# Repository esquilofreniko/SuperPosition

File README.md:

**SuperPosition – Rev 1**

**Bill of Materials:**

|Function / Name 		|# |Note 								|Part Number 		|
|-----------------------|--|------------------------------------|-------------------|
|MCU Teensy 3.5/3.6 	|1 |Cut USB power trace 				|DEV-14057 			|
|Display OLED SSD1306 	|1 |SSD1306 / SPI / 0.96’’ / 128x64 [1] | 					|
|Adafruit NeoTrellis 	|1 |4x4 RGB LED Button Matrix [2] 		|Mouser: 485-1616 	|
|Silicone 4x4 Keypad 	|1 |Silicone Elastomer Button Keypad [3]|Mouser: 485-1611 	|
|Rotary Encoder 		|2 |24 Pulse Mechanical Rotary Encoder 	|PEC11R-4220F -S0024|
|Tactile Switch 		|2 |9.4mm Black Button Tactile Switch 	|2-1825910-7 		|
|3.5mm Jacks 			|12 |“Thonkiconn” Mono Jacks from Thonk |PJ398SM 			|
|DAC MCP4922 			|2 |12-bit Digital to Analog Converter 	|MCP4922-E/P 		|
|Op-amp MCP6004 		|1 |Operational Amplifier 				|MCP6004-E/P 		|
|Op-amp TL04CN 			|2 |Operational Amplifier 				|TL074CN 			|
|Regulator L7805 		|1 |5V Voltage Regulator 				|L7805CP 			|
|Diode 1N5817 			|2 |Through Hole 						|1N5817 			|
|Resistor 100k SMD 0805 |24|0.1% 								| 					|
|Resistor 56k SMD 0805 	|4 |0.1% 								| 					|
|Resistor 1k SMD 0805 	|8 |1% 									| 					|
|Capacitor 10u SMD 0805 |2 |Ceramic Capacitor 					| 					|
|Capacitor 100n SMD 0805|6 |Ceramic Capacitor 					|					|

[1] https://www.amazon.co.uk/IZOKEE-Display-SSD1306-Raspberry-White-IIC/dp/B076PKKTRP/ref=sr_1_fkmr0_1?keywords=ssd1306%2Bspy%2B0.96%27%27&qid=1557409352&s=electronics&sr=1-1-fkmr0&th=1

[2] https://www.adafruit.com/product/3954

[3] https://www.adafruit.com/product/1611

**Build Guide (work in progress):**  

1. Solder the 2 10u 0805 SMT Capacitors in the front;

2. Solder the 6 100n 0805 SMT Capacitors in the back;

3. Solder all the 0805 SMT Resistors in the back;

4. Solder the 1N5817 Diodes in the back;

5. Solder the L7805 Voltage Regulator in the back;

6. Solder the Power Header in the back;

7. Solder the pin sockets for the teensy in the back;

8. Solder the ICs in the front (MCP6004, TL074CN, MCP4922);

9. Solder the buttons and encoders in the front;

10. Solder all of the jacks on the top;

11. Solder the Adafruit NeoTrellis PCB in the front;

12. Solder the OLED Display in the front;

13. Place the Panel on the front of the PCB;

14. Cut the USB power trace on the back of the teensy;

15. Place the teensy on the back;

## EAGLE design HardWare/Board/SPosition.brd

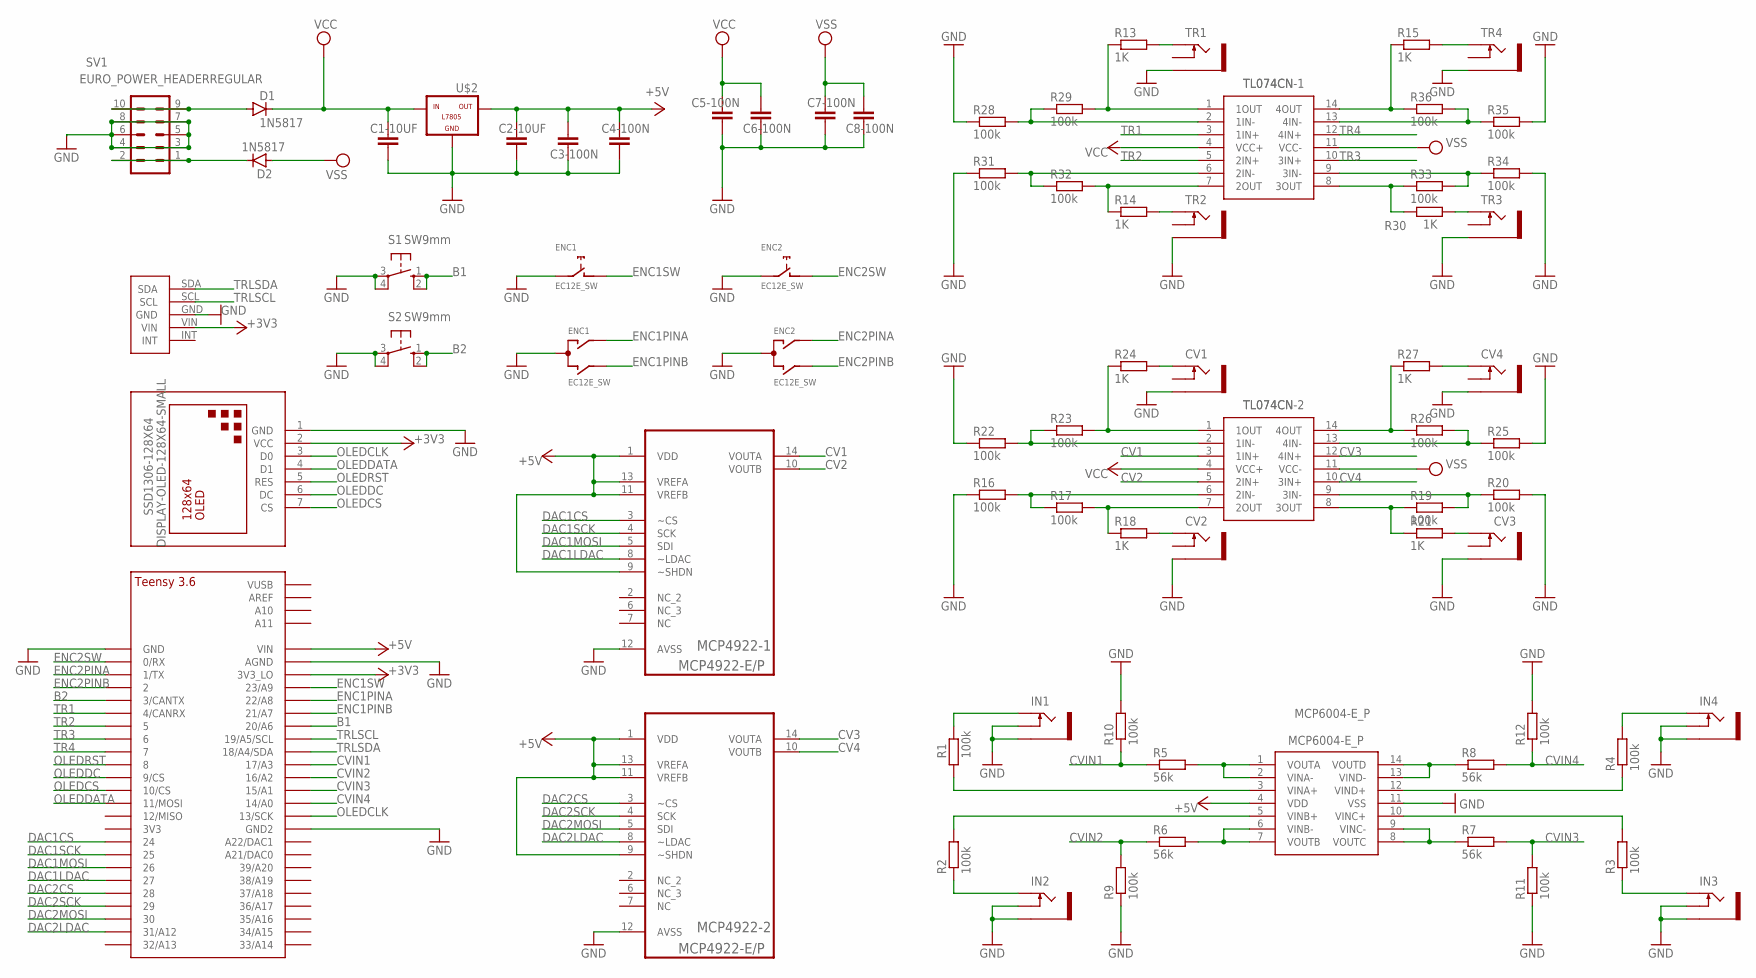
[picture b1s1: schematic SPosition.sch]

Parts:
C1-10UF, C2-10UF: 10uF; C0805
C3-100N, C4-100N, C5-100N, C6-100N, C7-100N, C8-100N: 100n; C0805
CV1, CV2, CV3, CV4: THONKICONNNEW; WQP-PJ301M-12_JACK
D1, D2: 1N5817; DO41-10
ENC1, ENC2: EC12E_SW; ALPS_EC12E_SW
IN1, IN2, IN3, IN4: THONKICONNNEW; WQP-PJ301M-12_JACK
MCP4922-1, MCP4922-2: MCP4922-E/P; DIP254P762X533-14
MCP6004-E_P: MCP6004-E_P; DIP781W56P254L1918H533Q14N
R1, R2, R3, R4, R9, R10, R11, R12, R16, R17, R19, R20, R22, R23, R25, R26, R28, R29, R31, R32, R33, R34, R35, R36: 100k; R0805
R5, R6, R7, R8: 56k; R0805
R13, R14, R15, R18, R21, R24, R27, R30: 1K; R0805
S1, S2: SW9mm; B3F-10XX
SSD1306-128X64: DISPLAY-OLED-128X64-SMALL
SV1: EURO_POWER_HEADERREGULAR; EURO_POWER_HEADER
TL074CN-1, TL074CN-2: TL074CN; DIP794W53P254L1930H508Q14N
TR1, TR2, TR3, TR4: THONKICONNNEW; WQP-PJ301M-12_JACK
U$1: TEENSY_3.5/3.6_BASIC
U$2: -L7805; L7805
U$4: SPREV5

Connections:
+3V3: SSD1306-128X64.2 (VCC), U$1.3V3_LO, U$4.VIN
+5V: C2-10UF.1, C3-100N.1, C4-100N.1, MCP4922-1.1 (VDD), MCP4922-1.9 (~SHDN), MCP4922-1.11 (VREFB), MCP4922-1.13 (VREFA), MCP4922-2.1 (VDD), MCP4922-2.9 (~SHDN), MCP4922-2.11 (VREFB), MCP4922-2.13 (VREFA), MCP6004-E_P.4 (VDD), U$1.VIN, U$2.OUT
B1: S1.1 (S), S1.2 (S1), U$1.20/A6
B2: S2.1 (S), S2.2 (S1), U$1.3/CANTX
CV1: MCP4922-1.14 (VOUTA), TL074CN-2.3 (1IN+)
CV2: MCP4922-1.10 (VOUTB), TL074CN-2.5 (2IN+)
CV3: MCP4922-2.14 (VOUTA), TL074CN-2.12 (4IN+)
CV4: MCP4922-2.10 (VOUTB), TL074CN-2.10 (3IN+)
CVIN1: R5.1, R10.1, U$1.17/A3
CVIN2: R6.1, R9.2, U$1.16/A2
CVIN3: R7.2, R11.2, U$1.15/A1
CVIN4: R8.2, R12.1, U$1.14/A0
DAC1CS: MCP4922-1.3 (~CS), U$1.24
DAC1LDAC: MCP4922-1.8 (~LDAC), U$1.27
DAC1MOSI: MCP4922-1.5 (SDI), U$1.26
DAC1SCK: MCP4922-1.4 (SCK), U$1.25
DAC2CS: MCP4922-2.3 (~CS), U$1.28
DAC2LDAC: MCP4922-2.8 (~LDAC), U$1.31/A12
DAC2MOSI: MCP4922-2.5 (SDI), U$1.30
DAC2SCK: MCP4922-2.4 (SCK), U$1.29
ENC1PINA: ENC1.A, U$1.22/A8
ENC1PINB: ENC1.B, U$1.21/A7
ENC1SW: ENC1.D (1), U$1.23/A9
ENC2PINA: ENC2.A, U$1.1/TX
ENC2PINB: ENC2.B, U$1.2
ENC2SW: ENC2.D (1), U$1.0/RX
GND: C1-10UF.2, C2-10UF.2, C3-100N.2, C4-100N.2, C5-100N.2, C6-100N.2, C7-100N.2, C8-100N.2, CV1.P$3_SLEEVE (SLEEVE), CV2.P$3_SLEEVE (SLEEVE), CV3.P$3_SLEEVE (SLEEVE), CV4.P$3_SLEEVE (SLEEVE), ENC1.C, ENC1.E (2), ENC2.C, ENC2.E (2), IN1.P$2_SWITCH (SWITCH), IN1.P$3_SLEEVE (SLEEVE), IN2.P$2_SWITCH (SWITCH), IN2.P$3_SLEEVE (SLEEVE), IN3.P$2_SWITCH (SWITCH), IN3.P$3_SLEEVE (SLEEVE), IN4.P$2_SWITCH (SWITCH), IN4.P$3_SLEEVE (SLEEVE), MCP4922-1.12 (AVSS), MCP4922-2.12 (AVSS), MCP6004-E_P.11 (VSS), R9.1, R10.2, R11.1, R12.2, R16.1, R20.2, R22.1, R25.2, R28.1, R31.1, R34.2, R35.2, S1.3, S1.4 (P1), S2.3, S2.4 (P1), SSD1306-128X64.1 (GND), SV1.3, SV1.4, SV1.5, SV1.6, SV1.7, SV1.8, TR1.P$3_SLEEVE (SLEEVE), TR2.P$3_SLEEVE (SLEEVE), TR3.P$3_SLEEVE (SLEEVE), TR4.P$3_SLEEVE (SLEEVE), U$1.AGND, U$1.GND, U$1.GND2, U$2.GND, U$4.GND
unnamed: D1.A, SV1.9, SV1.10
unnamed: R17.2, R18.1, TL074CN-2.7 (2OUT)
unnamed: IN1.P$1_TIP (TIP), R1.2
unnamed: MCP6004-E_P.6 (VINB-), MCP6004-E_P.7 (VOUTB), R6.2
unnamed: IN2.P$1_TIP (TIP), R2.1
unnamed: IN3.P$1_TIP (TIP), R3.1
unnamed: R14.1, R32.2, TL074CN-1.7 (2OUT)
unnamed: IN4.P$1_TIP (TIP), R4.2
unnamed: MCP6004-E_P.5 (VINB+), R2.2
unnamed: MCP6004-E_P.13 (VIND-), MCP6004-E_P.14 (VOUTD), R8.1
unnamed: MCP6004-E_P.8 (VOUTC), MCP6004-E_P.9 (VINC-), R7.1
unnamed: MCP6004-E_P.3 (VINA+), R1.1
unnamed: MCP6004-E_P.10 (VINC+), R3.2
unnamed: MCP6004-E_P.12 (VIND+), R4.1
unnamed: R16.2, R17.1, TL074CN-2.6 (2IN-)
unnamed: MCP6004-E_P.1 (VOUTA), MCP6004-E_P.2 (VINA-), R5.2
unnamed: CV2.P$1_TIP (TIP), R18.2
unnamed: CV3.P$1_TIP (TIP), R21.2
unnamed: R19.1, R21.1, TL074CN-2.8 (3OUT)
unnamed: R19.2, R20.1, TL074CN-2.9 (3IN-)
unnamed: R22.2, R23.1, TL074CN-2.2 (1IN-)
unnamed: R23.2, R24.1, TL074CN-2.1 (1OUT)
unnamed: CV1.P$1_TIP (TIP), R24.2
unnamed: R25.1, R26.2, TL074CN-2.13 (4IN-)
unnamed: R26.1, R27.1, TL074CN-2.14 (4OUT)
unnamed: CV4.P$1_TIP (TIP), R27.2
unnamed: D2.C, SV1.1, SV1.2
unnamed: R28.2, R29.1, TL074CN-1.2 (1IN-)
unnamed: R13.1, R29.2, TL074CN-1.1 (1OUT)
unnamed: R31.2, R32.1, TL074CN-1.6 (2IN-)
unnamed: R13.2, TR1.P$1_TIP (TIP)
unnamed: R14.2, TR2.P$1_TIP (TIP)
unnamed: R33.2, R34.1, TL074CN-1.9 (3IN-)
unnamed: R30.2, TR3.P$1_TIP (TIP)
unnamed: R30.1, R33.1, TL074CN-1.8 (3OUT)
unnamed: R35.1, R36.2, TL074CN-1.13 (4IN-)
unnamed: R15.1, R36.1, TL074CN-1.14 (4OUT)
unnamed: R15.2, TR4.P$1_TIP (TIP)
OLEDCLK: SSD1306-128X64.3 (D0), U$1.13/SCK
OLEDCS: SSD1306-128X64.7 (CS), U$1.10/CS
OLEDDATA: SSD1306-128X64.4 (D1), U$1.11/MOSI
OLEDDC: SSD1306-128X64.6 (DC), U$1.9/CS
OLEDRST: SSD1306-128X64.5 (RES), U$1.8
TR1: TL074CN-1.3 (1IN+), U$1.4/CANRX
TR2: TL074CN-1.5 (2IN+), U$1.5
TR3: TL074CN-1.10 (3IN+), U$1.6
TR4: TL074CN-1.12 (4IN+), U$1.7
TRLSCL: U$1.19/A5/SCL, U$4.SCL
TRLSDA: U$1.18/A4/SDA, U$4.SDA
VCC: C1-10UF.1, C5-100N.1, C6-100N.1, D1.C, TL074CN-1.4 (VCC+), TL074CN-2.4 (VCC+), U$2.IN
VSS: C7-100N.1, C8-100N.1, D2.A, TL074CN-1.11 (VCC-), TL074CN-2.11 (VCC-)

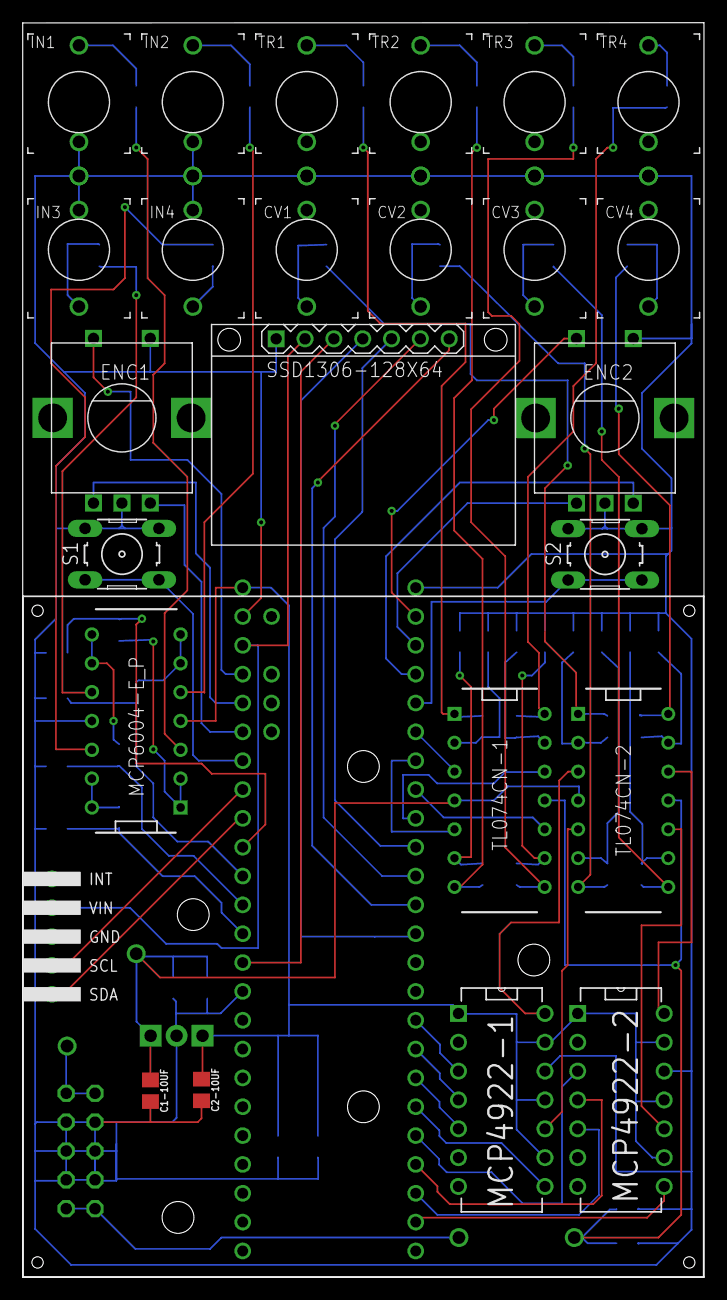
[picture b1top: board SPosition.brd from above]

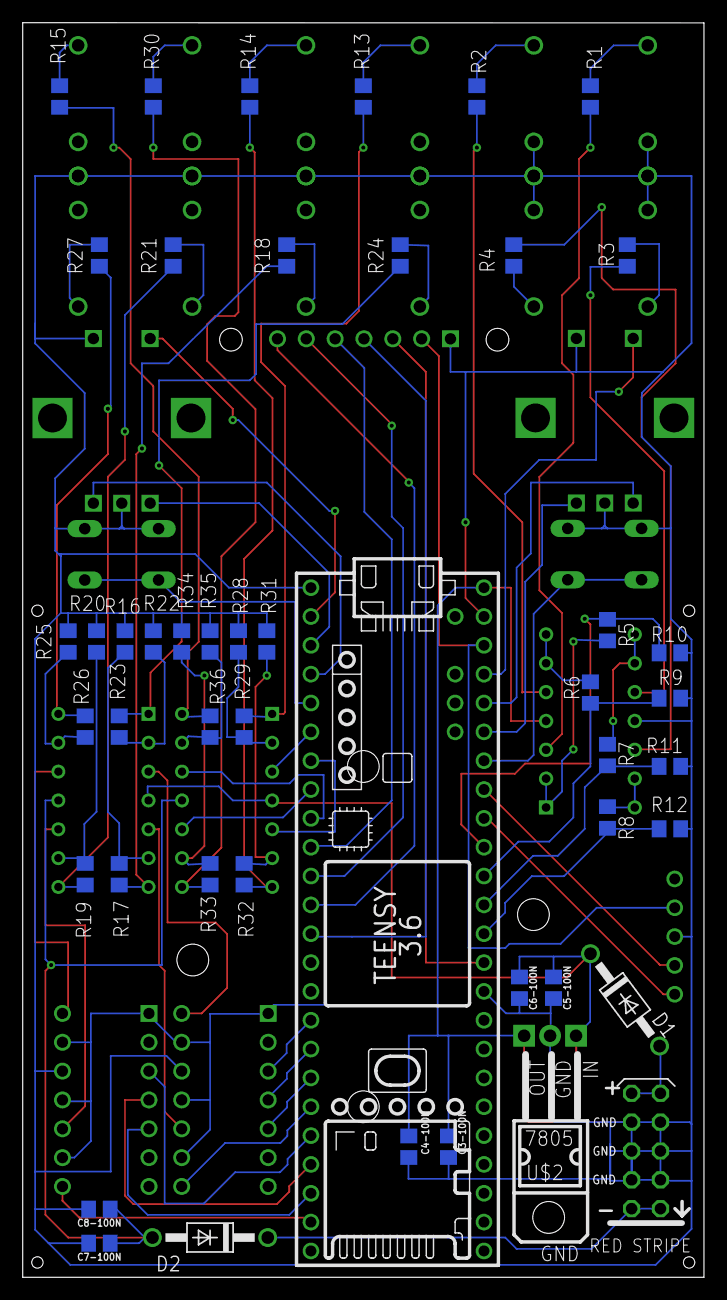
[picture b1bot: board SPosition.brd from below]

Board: 2 copper layers, 60.0 x 110.5 mm, 72 parts (47 on the bottom side), 78 nets.

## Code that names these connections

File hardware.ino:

#define B1PIN 17
#define B2PIN 12

#define ENC1BUTTON 0
#define ENC1PINA 1
#define ENC1PINB 2
#define ENC2BUTTON 14
#define ENC2PINA 15
#define ENC2PINB 16

#define OLED_RESET  8
#define OLED_DC     9
#define OLED_CS     10
#define OLED_MOSI   11
#define OLED_CLK   13

void hardware_init(){
  button_init();
  encoder_init();
  keypad_init();
  oled_init();
}

void hardware_read(){
  button_read();
  encoder_read();
  keypad_read();
}

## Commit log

2019-01-22 stuff
2019-01-22 midi
2019-01-22 midi working
2019-01-22 fixed latency :D
2019-01-23 fixes
2019-01-23 mooore
2019-01-23 better oled
2019-01-23 faster oled
2019-01-23 started schematic
2019-02-06 added LEDS
2019-02-06 optimized LEDS
2019-02-06 adding 2nd encoder
2019-02-06 added 2nd encoder
2019-02-08 added pannel
2019-02-09 relplaced monochrome keypad with rgb keypad
2019-02-12 schematic finished
2019-02-12 schematic improved
2019-02-13 improved schematic
2019-02-13 changed teensy 3.2 to 3.6
2019-02-15 improved schem
2019-02-15 improved cod
2019-02-17 pcb and eagle sch
2019-02-18 changed to 128x64 OLED, improved schematic and code (latency)
2019-02-18 improved code latency
2019-02-18 changed oled display library to faster one
2019-02-18 fixed issues with held encoder
2019-02-18 better code (classes)
2019-02-19 better code
2019-02-19 added opamp for cv input buffering
2019-02-20 improved circuit and pcb£
2019-02-20 updated circuit and pcb
2019-02-21 finished schematic
2019-02-21 better pcb
2019-02-23 finished pcb
2019-02-24 better oled speed and better code
2019-02-25 better code (recovered lost work on merge)
2019-02-25 fixed oled
2019-02-25 debuging
2019-02-25 64step
2019-02-25 added functionality
2019-02-25 added second view mode (horizontal oposed to cartesian)
2019-02-25 improved horizontal view mode
2019-02-25 debbuging
2019-02-25 adding feautures
2019-02-26 debug
2019-02-27 more modular code
2019-02-27 debugging
2019-03-01 4 clocks
2019-03-01 added clock division
2019-03-01 debugging, clock division per step
2019-03-01 added length pararameter
2019-03-01 variable length
2019-03-02 debugging horizontal view
2019-03-02 interface design
2019-03-02 improvements
2019-03-11 rev 2 pcb
2019-03-12 new pcb and schematic
2019-03-12 new pcb and pannel
2019-03-12 renamed!
2019-03-12 re-organizing directories
2019-03-12 pcb and pannel redesign
2019-03-12 board and schem revisions
2019-03-12 schematic and pcb rev4
2019-03-12 noise reduction capacitors
2019-03-12 updated pcb and schematic
2019-03-12 pcb optimization
2019-03-13 pcb rev5
2019-03-14 added gerber files
2019-03-17 optimized code
2019-03-19 added menu
2019-03-19 updated CV Seq
2019-03-20 added quantizer
2019-03-20 optimization
2019-03-21 debugged quantizer
2019-03-21 improvements to UI
2019-03-27 pcb and pannel revision
2019-04-05 prototype finalized
2019-04-05 added all analog interfacing functions
2019-04-16 tested
2019-04-16 many bug fixes
2019-04-17 removed midi, debugging, fixed timing errors
2019-04-17 fixed sync issues
2019-04-17 better UI
2019-04-17 bug fixes
2019-04-17 bugfixes, better UI
2019-04-17 implemented ratcheting
2019-04-17 better ratcheting
2019-04-17 debuging... improved UI
2019-04-17 debuging... improved U
2019-04-17 added slew
2019-05-02 fixed gates
2019-05-04 added preset saving
2019-05-09 superposition
2019-05-09 added readme

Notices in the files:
parts and their libraries:
diy-modules: Released under the Creative Commons Attribution 4.0 International License: http://creativecommons.org/licenses/by/4.0
